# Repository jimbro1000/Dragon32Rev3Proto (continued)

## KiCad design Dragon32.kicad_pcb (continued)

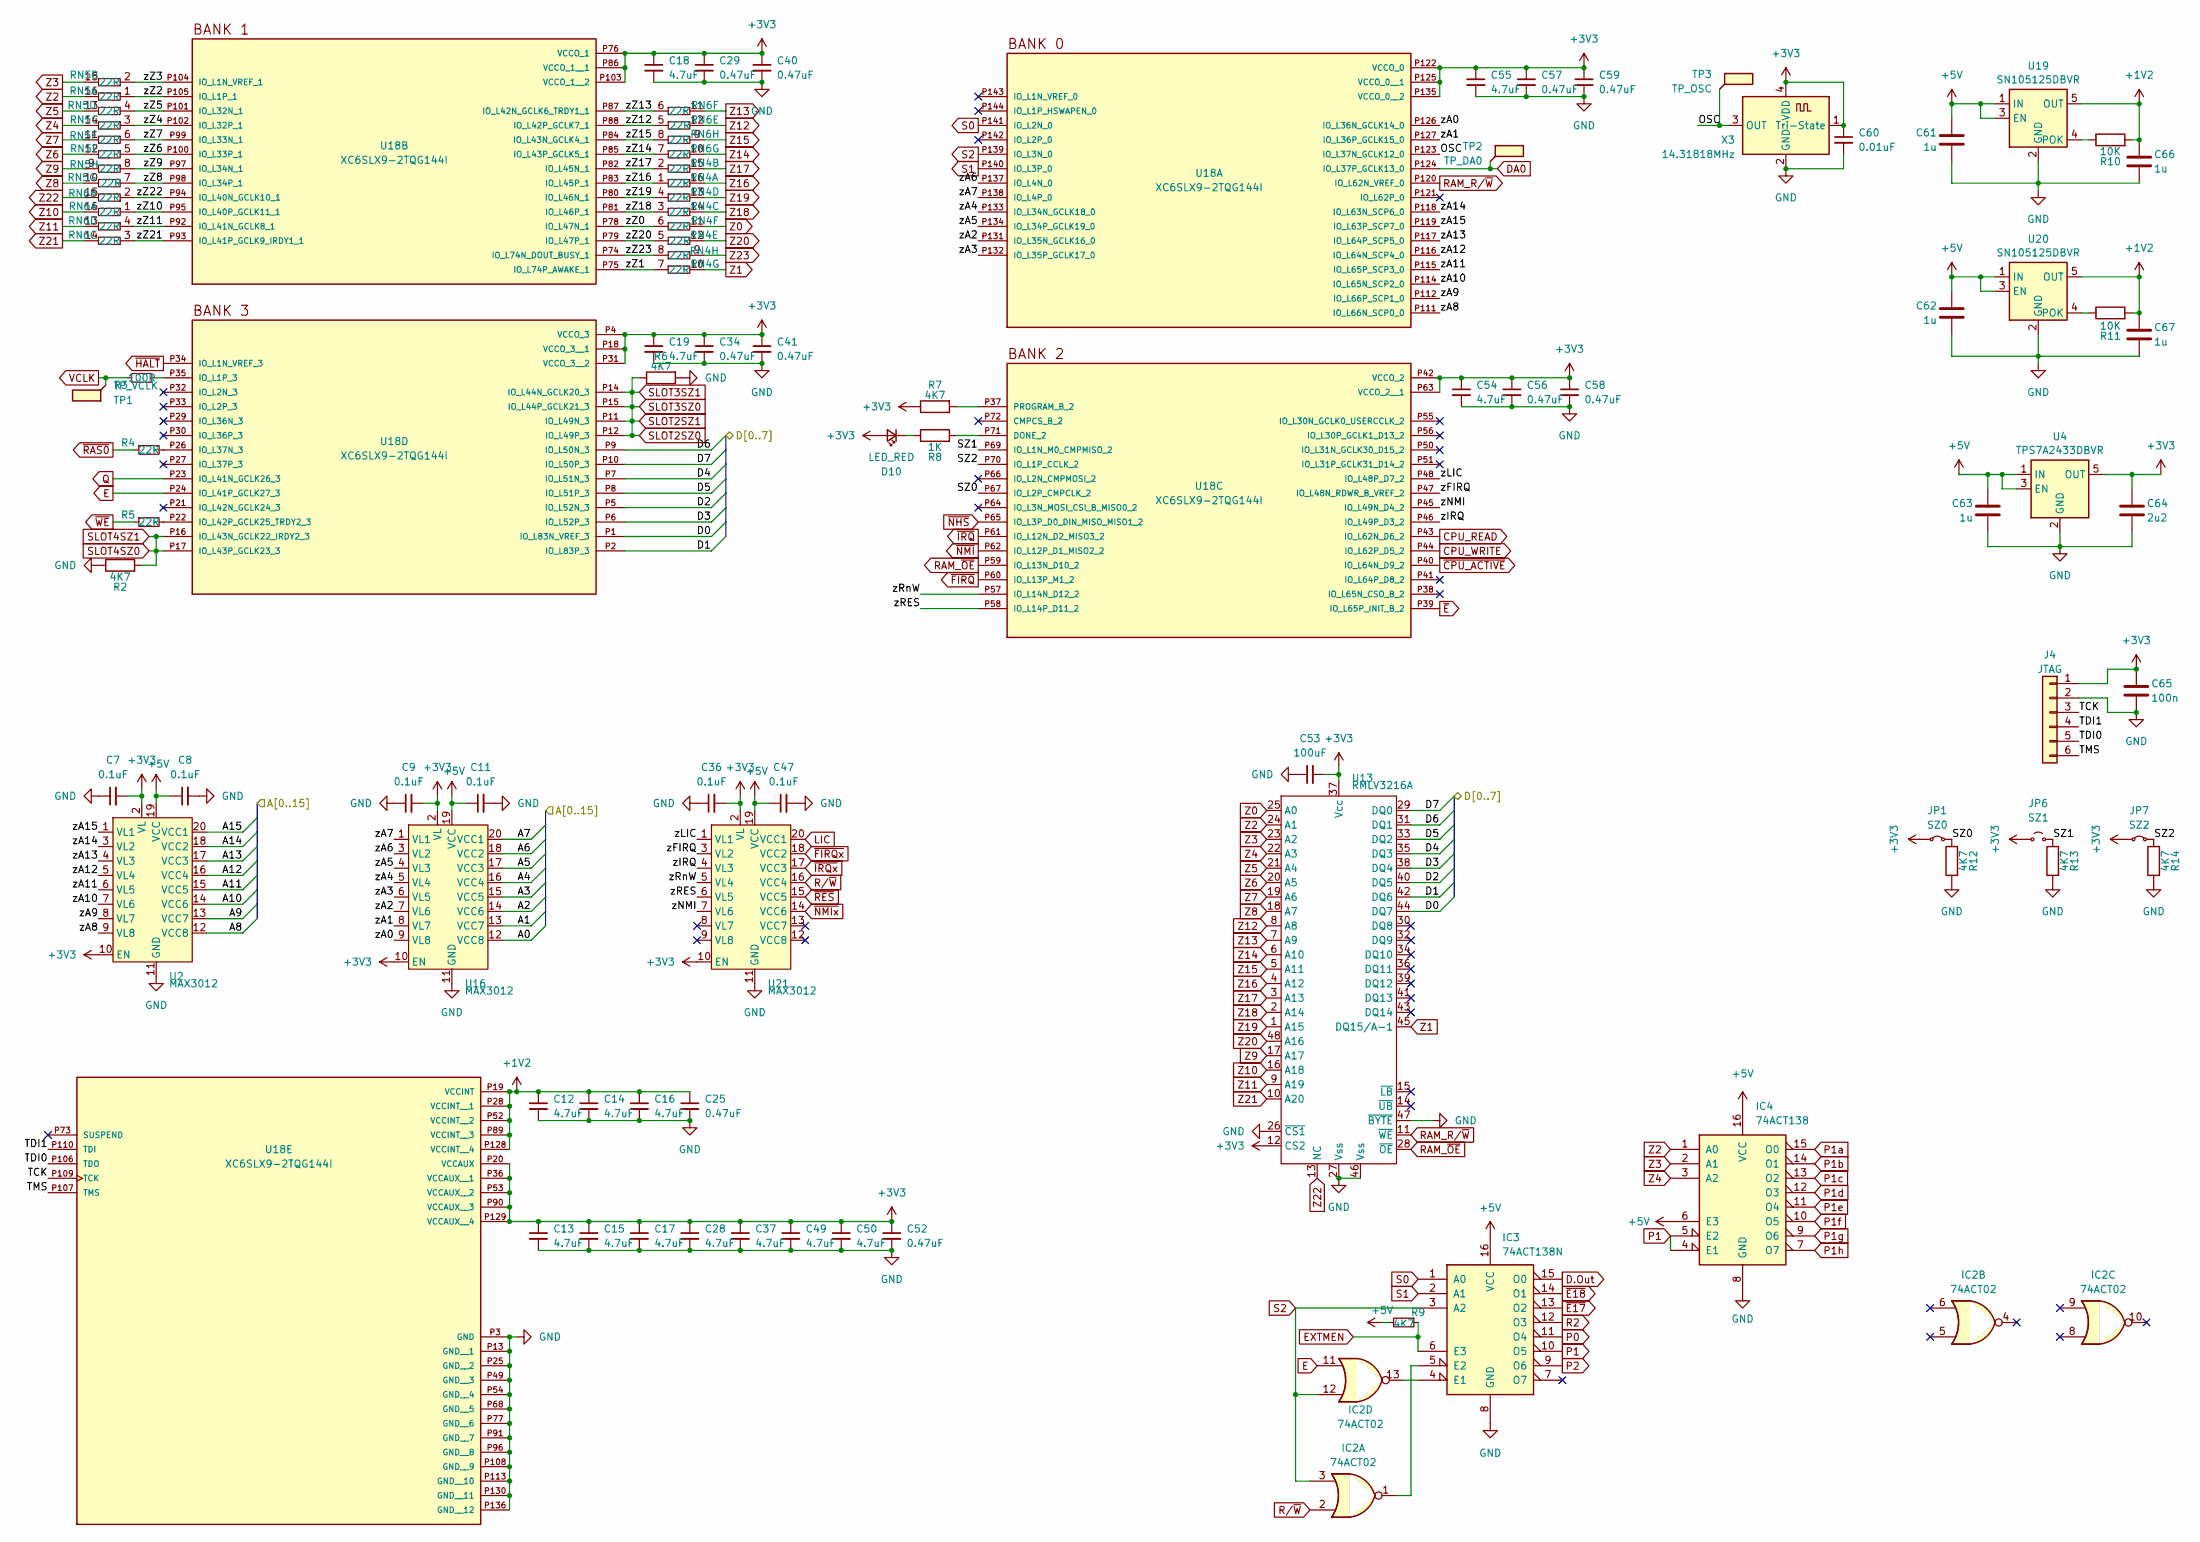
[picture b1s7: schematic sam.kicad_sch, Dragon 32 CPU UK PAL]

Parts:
C7, C8, C9, C11, C36, C47: 0.1uF; C_0805_2012Metric_Pad1.18x1.45mm_HandSolder; DigiKey 399-C0805C104K4RAC7800CT-ND
C12, C13, C14, C15, C16, C17, C18, C19, C28, C37, C49, C50, C54, C55: 4.7uF; C_0805_2012Metric_Pad1.18x1.45mm_HandSolder; DigiKey 399-C0805C475K4RAC7800CT-ND
C25, C29, C34, C40, C41, C52, C56, C57, C58, C59: 0.47uF; C_0805_2012Metric_Pad1.18x1.45mm_HandSolder; DigiKey 399-C0805C474K4RAC7800CT-ND
C53: 100uF; C_0805_2012Metric_Pad1.18x1.45mm_HandSolder
C60: 0.01uF; C_0805_2012Metric_Pad1.18x1.45mm_HandSolder; DigiKey 399-C0805C103K4RAC7800CT-ND
C61, C62, C66, C67: 1u; C_0805_2012Metric_Pad1.18x1.45mm_HandSolder; DigiKey 399-C0805C105K4RAC7800CT-ND
C63: 1u; C_0805_2012Metric_Pad1.18x1.45mm_HandSolder; LCSC Part C77080
C64: 2u2; C_0805_2012Metric_Pad1.18x1.45mm_HandSolder; LCSC Part C961513
C65: 100n; C_0805_2012Metric_Pad1.18x1.45mm_HandSolder; JLCPCB BOM 0
D10: LED_RED; LED_0805_2012Metric; DigiKey 67-SML-LXF0805SRD-TRCT-ND
IC2: 74ACT02; SOIC-14_3.9x8.7mm_P1.27mm; DigiKey MC74ACT02DR2GOSCT-ND
IC3: 74ACT138N; SOIC-16W_7.5x10.3mm_P1.27mm; DigiKey 74ACT138SCXCT-ND
IC4: 74ACT138; SOIC-16W_7.5x10.3mm_P1.27mm; DigiKey 74ACT138SCXCT-ND
J4: JTAG; PinHeader_1x06_P2.54mm_Vertical; JLCPCB BOM 0
JP1: SZ0; SolderJumper-2_P1.3mm_Bridged_Pad1.0x1.5mm
JP6: SZ1; SolderJumper-2_P1.3mm_Open_Pad1.0x1.5mm
JP7: SZ2; SolderJumper-2_P1.3mm_Bridged_Pad1.0x1.5mm
R2, R6, R7, R12, R13, R14: 4K7; R_0805_2012Metric_Pad1.20x1.40mm_HandSolder; DigiKey 541-4131-1-ND
R3: 100R; R_0805_2012Metric_Pad1.20x1.40mm_HandSolder; DigiKey RNCP0805FTD100RCT-ND
R4, R5: 22R; R_0805_2012Metric_Pad1.20x1.40mm_HandSolder; DigiKey RPC0805JT22R0CT-ND
R8: 1K; R_0805_2012Metric_Pad1.20x1.40mm_HandSolder; DigiKey RNCP0805FTD1K00CT-ND
R9: 4K7; R_0805_2012Metric_Pad1.20x1.40mm_HandSolder; DigiKey CF14JT4K70CT-ND
R10, R11: 10K; R_0805_2012Metric_Pad1.20x1.40mm_HandSolder; DigiKey RNCP0805FTD10K0CT-ND
RN4, RN6: 22R; SOIC-16W_5.3x10.2mm_P1.27mm
RN5: 22R; SOIC-16W_5.3x10.2mm_P1.27mm; DigiKey 4816P-T01-220LF-ND
TP1: TP_VCLK; TestPoint_Loop_D1.80mm_Drill1.0mm_Beaded
TP2: TP_DA0; TestPoint_Loop_D1.80mm_Drill1.0mm_Beaded
TP3: TP_OSC; TestPoint_Loop_D1.80mm_Drill1.0mm_Beaded
U2, U16, U21: MAX3012; TSSOP-20_4.4x6.5mm_P0.65mm; DigiKey MAX3012EUP+-ND
U4: TPS7A2433DBVR; SOT-23-5; LCSC Part C2866134
U13: RMLV3216A; TSOP-I-48_18.4x12mm_P0.5mm; DigiKey RMLV3216AGSA-5S2#AA0-ND
U18: XC6SLX9-2TQG144I; AMD-LQFP-144; DigiKey 122-1748-ND
U19, U20: SN105125DBVR; SOT-23-5; DigiKey 296-15347-1-ND
X3: 14.31818MHz; Oscillator_SMD_ECS_2520MV-xxx-xx-4Pin_2.5x2.0mm; DigiKey XC1405CT-ND

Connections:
+1V2: C12.1, C14.1, C16.1, C25.1, C66.1, C67.1, R10.2, R11.2, U18.P19 (VCCINT), U18.P28 (VCCINT__1), U18.P52 (VCCINT__2), U18.P89 (VCCINT__3), U18.P128 (VCCINT__4), U19.5 (OUT), U20.5 (OUT)
/MPU/A0: U16.12 (VCC8); also elsewhere on the board
/MPU/A1: U16.13 (VCC7); also elsewhere on the board
/MPU/A2: U16.14 (VCC6); also elsewhere on the board
/MPU/A3: U16.15 (VCC5); also elsewhere on the board
/MPU/A4: U16.16 (VCC4); also elsewhere on the board
/MPU/A5: U16.17 (VCC3); also elsewhere on the board
/MPU/A6: U16.18 (VCC2); also elsewhere on the board
/MPU/A7: U16.20 (VCC1); also elsewhere on the board
/MPU/A13: U2.17 (VCC3); also elsewhere on the board
/MPU/A14: U2.18 (VCC2); also elsewhere on the board
/MPU/A15: U2.20 (VCC1); also elsewhere on the board
/MPU/D0: U13.44 (DQ7), U18.P1 (IO_L83N_VREF_3); also elsewhere on the board
/MPU/D1: U13.42 (DQ6), U18.P2 (IO_L83P_3); also elsewhere on the board
/MPU/D2: U13.40 (DQ5), U18.P5 (IO_L52N_3); also elsewhere on the board
/MPU/D3: U13.38 (DQ4), U18.P6 (IO_L52P_3); also elsewhere on the board
/MPU/D5: U13.33 (DQ2), U18.P8 (IO_L51P_3); also elsewhere on the board
/SAM/OSC: TP3.1, U18.P123 (IO_L37N_GCLK12_0), X3.3 (OUT)
/SAM/SZ0: JP1.2 (B), R12.1, U18.P67 (IO_L2P_CMPCLK_2)
/SAM/SZ1: JP6.2 (B), R13.1, U18.P69 (IO_L1N_M0_CMPMISO_2)
/SAM/SZ2: JP7.2 (B), R14.1, U18.P70 (IO_L1P_CCLK_2)
/SAM/TCK: J4.3, U18.P109 (TCK)
/SAM/TDI0: J4.5, U18.P106 (TDO)
/SAM/TDI1: J4.4, U18.P110 (TDI)
/SAM/TMS: J4.6, U18.P107 (TMS)
/SAM/zA0: U16.9 (VL8), U18.P126 (IO_L36N_GCLK14_0)
/SAM/zA1: U16.8 (VL7), U18.P127 (IO_L36P_GCLK15_0)
/SAM/zA2: U16.7 (VL6), U18.P131 (IO_L35N_GCLK16_0)
/SAM/zA3: U16.6 (VL5), U18.P132 (IO_L35P_GCLK17_0)
/SAM/zA4: U16.5 (VL4), U18.P133 (IO_L34N_GCLK18_0)
/SAM/zA5: U16.4 (VL3), U18.P134 (IO_L34P_GCLK19_0)
/SAM/zA6: U16.3 (VL2), U18.P137 (IO_L4N_0)
/SAM/zA7: U16.1 (VL1), U18.P138 (IO_L4P_0)
/SAM/zFIRQ: U18.P47 (IO_L48N_RDWR_B_VREF_2), U21.3 (VL2)
/SAM/zIRQ: U18.P46 (IO_L49P_D3_2), U21.4 (VL3)
/SAM/zLIC: U18.P48 (IO_L48P_D7_2), U21.1 (VL1)
/SAM/zNMI: U18.P45 (IO_L49N_D4_2), U21.7 (VL6)
/SAM/zRES: U18.P58 (IO_L14P_D11_2), U21.6 (VL5)
/SAM/zRnW: U18.P57 (IO_L14N_D12_2), U21.5 (VL4)
/SAM/zZ0: RN4.6, U18.P78 (IO_L47N_1)
/SAM/zZ1: RN4.7, U18.P75 (IO_L74P_AWAKE_1)
/SAM/zZ2: RN5.1, U18.P105 (IO_L1P_1)
/SAM/zZ3: RN5.2, U18.P104 (IO_L1N_VREF_1)
/SAM/zZ4: RN5.3, U18.P102 (IO_L32P_1)
/SAM/zZ5: RN5.4, U18.P101 (IO_L32N_1)
/SAM/zZ6: RN5.5, U18.P100 (IO_L33P_1)
/SAM/zZ7: RN5.6, U18.P99 (IO_L33N_1)
/SAM/zZ8: RN5.7, U18.P98 (IO_L34P_1)
/SAM/zZ9: RN5.8, U18.P97 (IO_L34N_1)
/SAM/zZ10: RN6.1, U18.P95 (IO_L40P_GCLK11_1)
/SAM/zZ11: RN6.4, U18.P92 (IO_L41N_GCLK8_1)
/SAM/zZ12: RN6.5, U18.P88 (IO_L42P_GCLK7_1)
/SAM/zZ13: RN6.6, U18.P87 (IO_L42N_GCLK6_TRDY1_1)
/SAM/zZ14: RN6.7, U18.P85 (IO_L43P_GCLK5_1)
/SAM/zZ15: RN6.8, U18.P84 (IO_L43N_GCLK4_1)
/SAM/zZ16: RN4.1, U18.P83 (IO_L45P_1)
/SAM/zZ17: RN4.2, U18.P82 (IO_L45N_1)
/SAM/zZ18: RN4.3, U18.P81 (IO_L46P_1)
/SAM/zZ19: RN4.4, U18.P80 (IO_L46N_1)
/SAM/zZ20: RN4.5, U18.P79 (IO_L47P_1)
/SAM/zZ21: RN6.3, U18.P93 (IO_L41P_GCLK9_IRDY1_1)
/SAM/zZ22: RN6.2, U18.P94 (IO_L40N_GCLK10_1)
/SAM/zZ23: RN4.8, U18.P74 (IO_L74N_DOUT_BUSY_1)
CPU_READ: U18.P43 (IO_L62N_D6_2); also elsewhere on the board
CPU_WRITE: U18.P44 (IO_L62P_D5_2); also elsewhere on the board
D.Out: IC3.15 (O0)
DA0: TP2.1, U18.P124 (IO_L37P_GCLK13_0); also elsewhere on the board
E: IC2.11, U18.P24 (IO_L41P_GCLK27_3); also elsewhere on the board
EXTMEN: IC3.6 (E3), R9.1; also elsewhere on the board
LIC: U21.20 (VCC1)
unnamed: D10.1 (K), R8.1
unnamed: IC2.13, IC3.4 (E1)
unnamed: IC2.1, IC3.5 (E2)
unnamed: R8.2, U18.P71 (DONE_2)
unnamed: R7.2, U18.P37 (PROGRAM_B_2)
unnamed: R3.2, U18.P35 (IO_L1P_3)
unnamed: R4.2, U18.P26 (IO_L37N_3)
unnamed: R5.2, U18.P22 (IO_L42P_GCLK25_TRDY2_3)
unnamed: R10.1, U19.4 (POK)
unnamed: R11.1, U20.4 (POK)
P0: IC3.11 (O4); also elsewhere on the board
P1: IC3.10 (O5), IC4.4 (E1), IC4.5 (E2)
P1a: IC4.15 (O0); also elsewhere on the board
P1b: IC4.14 (O1); also elsewhere on the board
P1c: IC4.13 (O2); also elsewhere on the board
P1d: IC4.12 (O3); also elsewhere on the board
P1e: IC4.11 (O4)
P1f: IC4.10 (O5)
P1g: IC4.9 (O6)
P1h: IC4.7 (O7)
P2: IC3.9 (O6); also elsewhere on the board
Q: U18.P23 (IO_L41N_GCLK26_3); also elsewhere on the board
R2: IC3.12 (O3); also elsewhere on the board
RAM_R/~W: U13.11 (~WE), U18.P120 (IO_L62N_VREF_0)
RAM_~OE: U13.28 (~OE), U18.P59 (IO_L13N_D10_2)
R/~W: IC2.2, U21.16 (VCC4); also elsewhere on the board
S0: IC3.1 (A0), U18.P141 (IO_L2N_0)
S1: IC3.2 (A1), U18.P140 (IO_L3P_0)
S2: IC2.3, IC2.12, IC3.3 (A2), U18.P139 (IO_L3N_0)
SLOT2SZ0: R6.1, U18.P11 (IO_L49N_3), U18.P12 (IO_L49P_3), U18.P14 (IO_L44N_GCLK20_3), U18.P15 (IO_L44P_GCLK21_3)
SLOT4SZ0: R2.2, U18.P16 (IO_L43N_GCLK22_IRDY2_3), U18.P17 (IO_L43P_GCLK23_3)
VCLK: R3.1, TP1.1; also elsewhere on the board
Z0: RN4.11, U13.25 (A0); also elsewhere on the board
Z1: RN4.10, U13.45 (DQ15/A-1); also elsewhere on the board
Z2: IC4.1 (A0), RN5.16, U13.24 (A1); also elsewhere on the board
Z3: IC4.2 (A1), RN5.15, U13.23 (A2); also elsewhere on the board
Z4: IC4.3 (A2), RN5.14, U13.22 (A3); also elsewhere on the board
Z5: RN5.13, U13.21 (A4); also elsewhere on the board
Z6: RN5.12, U13.20 (A5); also elsewhere on the board
Z7: RN5.11, U13.19 (A6); also elsewhere on the board
Z8: RN5.10, U13.18 (A7); also elsewhere on the board
Z9: RN5.9, U13.17 (A17); also elsewhere on the board
Z10: RN6.16, U13.16 (A18); also elsewhere on the board
Z11: RN6.13, U13.9 (A19); also elsewhere on the board
Z12: RN6.12, U13.8 (A8); also elsewhere on the board
Z13: RN6.11, U13.7 (A9); also elsewhere on the board
Z14: RN6.10, U13.6 (A10); also elsewhere on the board
Z15: RN6.9, U13.5 (A11); also elsewhere on the board
Z16: RN4.16, U13.4 (A12); also elsewhere on the board
Z17: RN4.15, U13.3 (A13); also elsewhere on the board
Z18: RN4.14, U13.2 (A14); also elsewhere on the board
Z19: RN4.13, U13.1 (A15)
Z20: RN4.12, U13.48 (A16)
Z21: RN6.14, U13.10 (A20)
Z22: RN6.15, U13.13 (NC)
Z23: RN4.9
~CPU_ACTIVE: U18.P40 (IO_L64N_D9_2)
~E17: IC3.13 (O2)
~E18: IC3.14 (O1)
~E: U18.P39 (IO_L65P_INIT_B_2); also elsewhere on the board
~FIRQx: U21.18 (VCC2); also elsewhere on the board
~FIRQ: U18.P60 (IO_L13P_M1_2); also elsewhere on the board
~HALT: U18.P34 (IO_L1N_VREF_3); also elsewhere on the board
~IRQx: U21.17 (VCC3); also elsewhere on the board
~IRQ: U18.P61 (IO_L12N_D2_MISO3_2); also elsewhere on the board
~NHS: U18.P65 (IO_L3P_D0_DIN_MISO_MISO1_2); also elsewhere on the board
~NMIx: U21.14 (VCC6); also elsewhere on the board
~NMI: U18.P62 (IO_L12P_D1_MISO2_2); also elsewhere on the board
~RAS0: R4.1; also elsewhere on the board
~RES: U21.15 (VCC5); also elsewhere on the board
~WE: R5.1

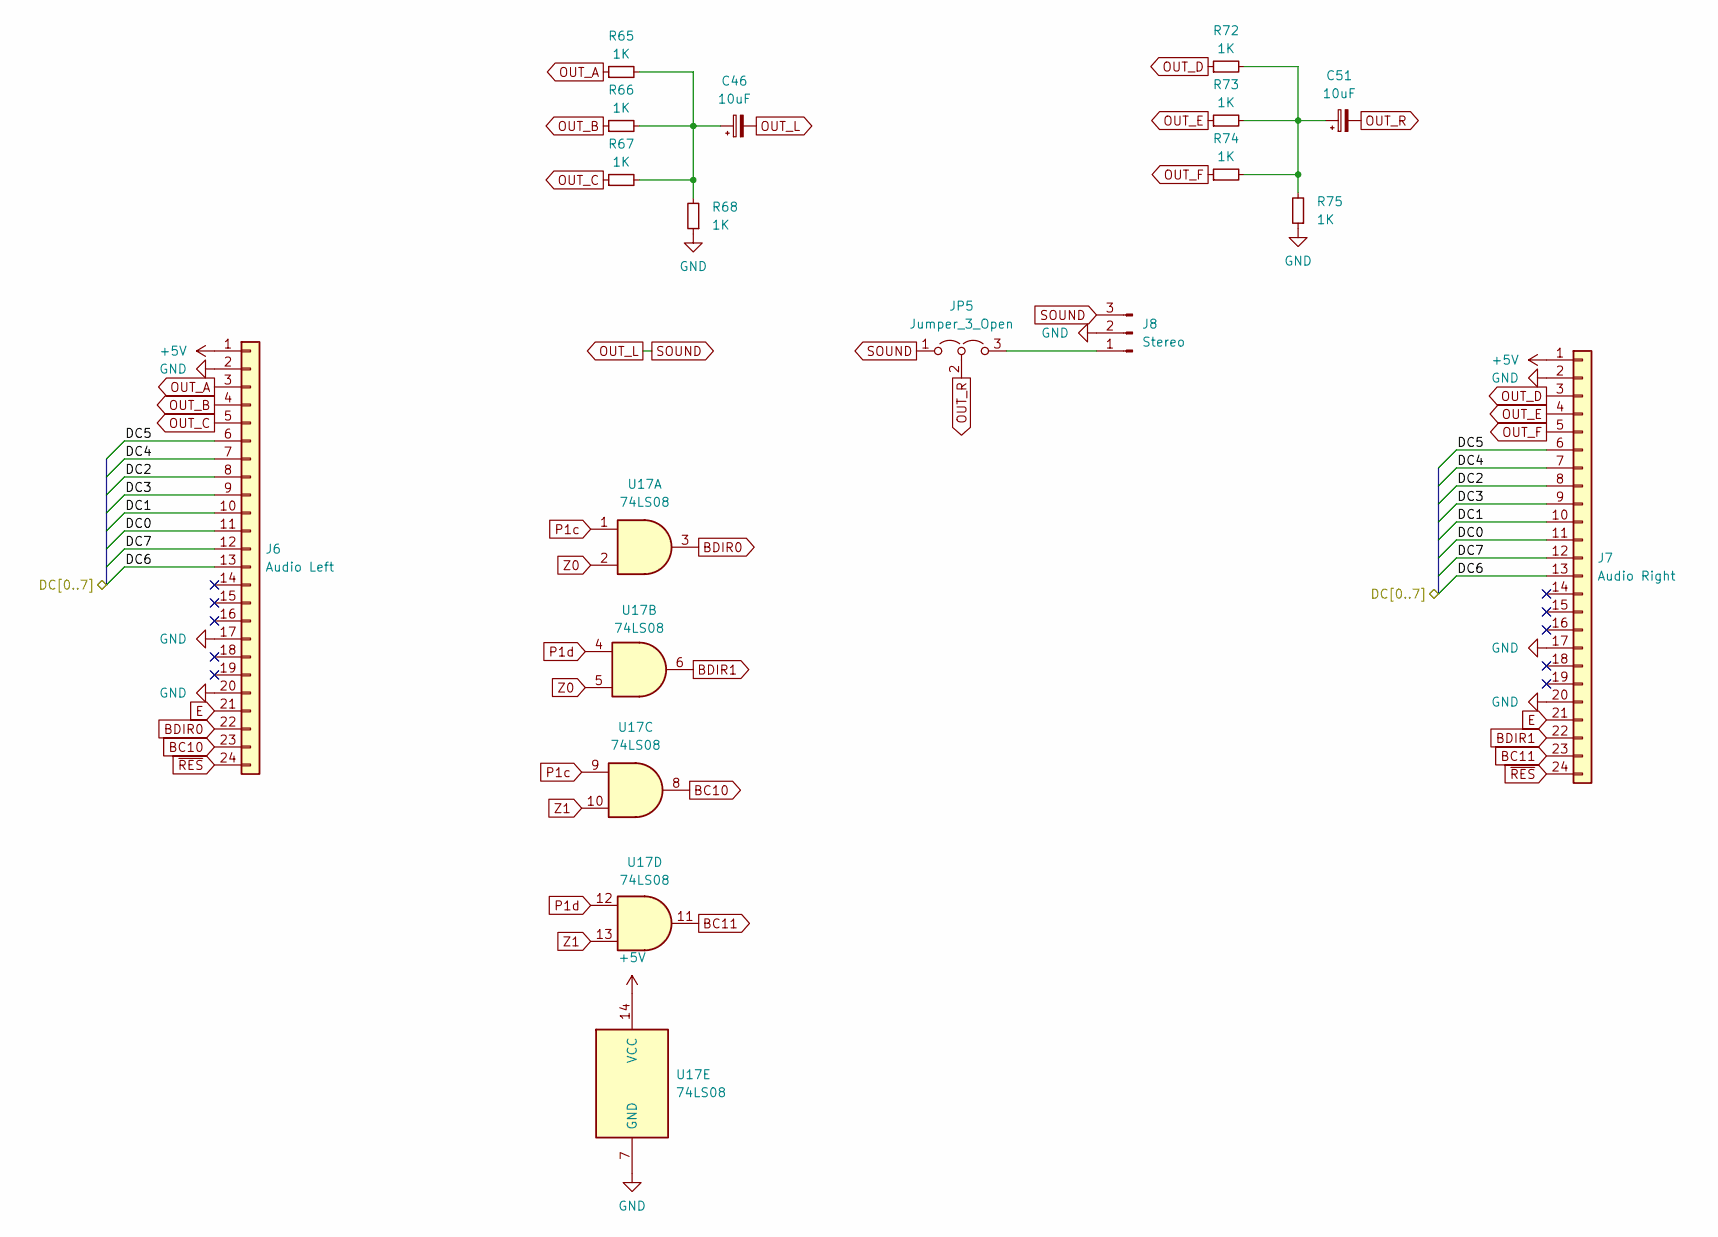
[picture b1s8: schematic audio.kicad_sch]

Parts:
C46, C51: 10uF; CP_Elec_5x3
J6: Audio Left; AY-QTHT
J7: Audio Right; AY-QTHT
J8: Stereo; PinHeader_1x03_P2.54mm_Vertical
JP5: Jumper_3_Open; PinHeader_1x03_P2.54mm_Vertical
R65, R66, R67, R68, R72, R73, R74, R75: 1K; R_0805_2012Metric_Pad1.20x1.40mm_HandSolder
U17: 74LS08; SO-14_3.9x8.65mm_P1.27mm

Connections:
/AUDIO/DC0: J6.11, J7.11; also elsewhere on the board
/AUDIO/DC1: J6.10, J7.10; also elsewhere on the board
/AUDIO/DC2: J6.8, J7.8; also elsewhere on the board
/AUDIO/DC3: J6.9, J7.9; also elsewhere on the board
/AUDIO/DC4: J6.7, J7.7; also elsewhere on the board
/AUDIO/DC5: J6.6, J7.6; also elsewhere on the board
/AUDIO/DC6: J6.13, J7.13; also elsewhere on the board
/AUDIO/DC7: J6.12, J7.12; also elsewhere on the board
BC10: J6.23, U17.8
BC11: J7.23, U17.11
BDIR0: J6.22, U17.3
BDIR1: J7.22, U17.6
E: J6.21, J7.21; also elsewhere on the board
unnamed: C46.1, R65.2, R66.2, R67.2, R68.2
unnamed: C51.1, R72.2, R73.2, R74.2, R75.2
unnamed: J8.1, JP5.3 (B)
OUT_A: J6.3, R65.1
OUT_B: J6.4, R66.1
OUT_C: J6.5, R67.1
OUT_D: J7.3, R72.1
OUT_E: J7.4, R73.1
OUT_F: J7.5, R74.1
OUT_L: C46.2, J8.3, JP5.1 (A); also elsewhere on the board
OUT_R: C51.2, JP5.2 (C)
P1c: U17.1, U17.9; also elsewhere on the board
P1d: U17.4, U17.12; also elsewhere on the board
Z0: U17.2, U17.5; also elsewhere on the board
Z1: U17.10, U17.13; also elsewhere on the board
~RES: J6.24, J7.24; also elsewhere on the board

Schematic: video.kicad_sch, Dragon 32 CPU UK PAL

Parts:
J1: Video Output Female; PinSocket_1x05_P2.54mm_Vertical
J2: Board Interconnect Female; PinSocket_2x11_P2.54mm_Vertical
J3: Conn_02x08_Odd_Even; PinSocket_2x08_P2.54mm_Vertical
PL6: Conn_01x09_Male; Molex_KK-396_A-41791-0009_1x09_P3.96mm_Vertical; DigiKey 2057-LHD-09-TS-ND

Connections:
+12V: PL6.9; also elsewhere on the board
-5V: J1.3, PL6.7; also elsewhere on the board
/MPU/D0: J2.3; also elsewhere on the board
/MPU/D1: J2.5; also elsewhere on the board
/MPU/D2: J2.7; also elsewhere on the board
/MPU/D3: J2.9; also elsewhere on the board
/MPU/D5: J2.13; also elsewhere on the board
BIAS: J1.1, PL6.1
CSS: J2.19; also elsewhere on the board
DA0: J2.6; also elsewhere on the board
E: J3.16; also elsewhere on the board
GM0: J2.14; also elsewhere on the board
GM1: J2.12; also elsewhere on the board
GM2: J2.10; also elsewhere on the board
OUT_L: PL6.3; also elsewhere on the board
P1b: J3.12; also elsewhere on the board
R/~W: J3.14; also elsewhere on the board
VCLK: J2.18; also elsewhere on the board
VID OUT: J1.4, PL6.4
~A/G: J2.20; also elsewhere on the board
~FS: J2.22; also elsewhere on the board
~NHS: J2.8; also elsewhere on the board
~RAS0: J2.16; also elsewhere on the board

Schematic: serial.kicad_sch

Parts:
C2, C20, C21, C24: 10u; CP_Elec_5x5.3
C10: 100n; C_0805_2012Metric_Pad1.18x1.45mm_HandSolder; not fitted
PL9: Serial; DIN-7_DELTRON_671-0701_Horizontal; not fitted
R44, R53: 4K7; R_0805_2012Metric_Pad1.20x1.40mm_HandSolder; DigiKey CF14JT4K70CT-ND; not fitted
U7: MAX232; SOIC-16_3.9x9.9mm_P1.27mm; DigiKey 296-14619-1-ND
U12: W65C51; PLCC-28_SMD-Socket; not fitted
X2: 1.8432MHz; Crystal_HC18-U_Horizontal_1EP_style2; not fitted

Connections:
+12V: R44.2; also elsewhere on the board
-5V: R53.2; also elsewhere on the board
/AUDIO/DC0: U12.18 (D0); also elsewhere on the board
/AUDIO/DC1: U12.19 (D1); also elsewhere on the board
/AUDIO/DC2: U12.20 (D2); also elsewhere on the board
/AUDIO/DC3: U12.21 (D3); also elsewhere on the board
/AUDIO/DC4: U12.22 (D4); also elsewhere on the board
/AUDIO/DC5: U12.23 (D5); also elsewhere on the board
/AUDIO/DC6: U12.24 (D6); also elsewhere on the board
/AUDIO/DC7: U12.25 (D7); also elsewhere on the board
/Serial/RxD: U7.12 (R1OUT), U12.12 (RXD)
/Serial/TxD: U7.11 (T1IN), U12.10 (TXD)
/Serial/xRxD: PL9.5, U7.13 (R1IN)
/Serial/xTxD: PL9.6, U7.14 (T1OUT)
/Serial/x~CTS: PL9.2, U7.8 (R2IN)
/Serial/x~DTR: PL9.4, U7.7 (T2OUT)
/Serial/~CTS: U7.9 (R2OUT), U12.9 (~CTS)
/Serial/~DTR: U7.10 (T2IN), U12.11 (~DTR)
E: U12.27 (E); also elsewhere on the board
unnamed: PL9.3, R44.1
unnamed: PL9.7, R53.1
unnamed: C2.1, U7.1 (C1+)
unnamed: C2.2, U7.3 (C1-)
unnamed: C21.1, U7.4 (C2+)
unnamed: C21.2, U7.5 (C2-)
unnamed: C20.1, U7.2 (VS+)
unnamed: C24.2, U7.6 (VS-)
unnamed: U12.6 (1XTAL), X2.1
unnamed: U12.7 (2XTAL), X2.2
P0: U12.3 (~CS1); also elsewhere on the board
R/~W: U12.28 (R/~W); also elsewhere on the board
Z0: U12.13 (RS0); also elsewhere on the board
Z1: U12.14 (RS1); also elsewhere on the board
Z2: U12.2 (CS0); also elsewhere on the board
~IRQx: U12.26 (~IRQ); also elsewhere on the board
~RES: U12.4 (~RESET); also elsewhere on the board

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
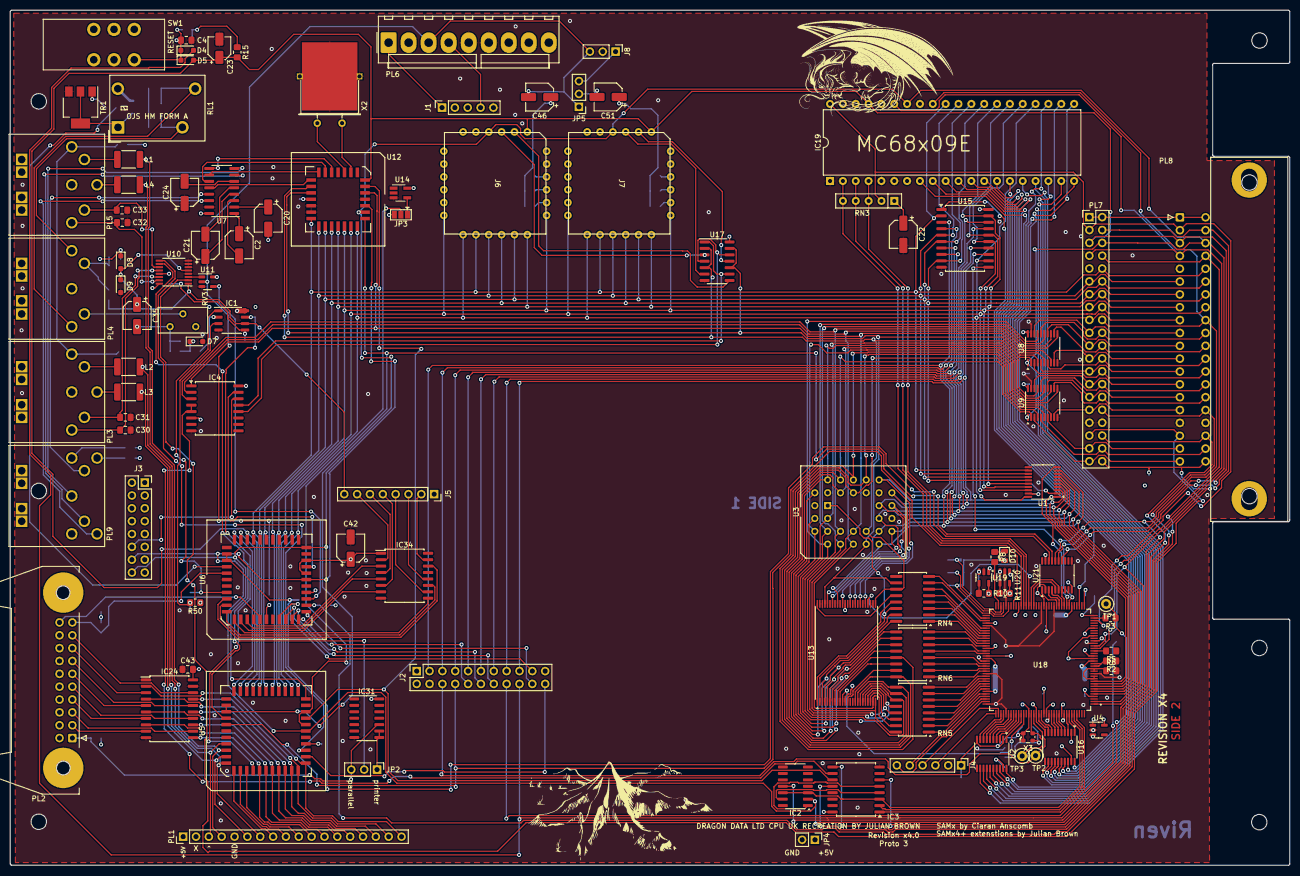
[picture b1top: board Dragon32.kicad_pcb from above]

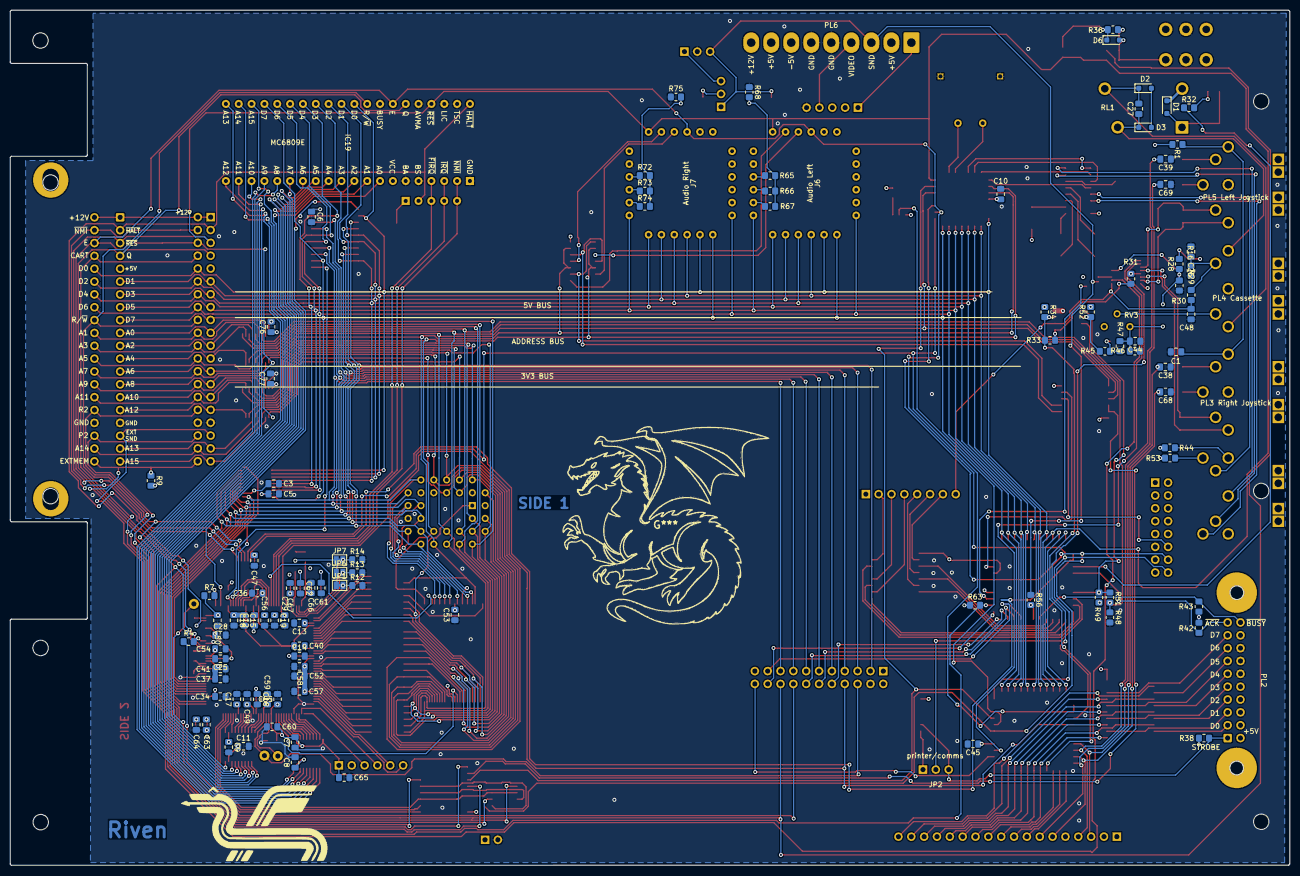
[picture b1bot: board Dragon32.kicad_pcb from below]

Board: 4 copper layers, 252.9 x 169.0 mm, 198 parts (100 on the bottom side), 295 nets.

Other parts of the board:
U10: 4052; TSSOP-16_4.4x5mm_P0.65mm
U11: TS5A3166DBVR; SOT-23-5

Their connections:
CB2: U11.4; also elsewhere on the board
ESND: U10.2 (Y2); also elsewhere on the board
unnamed: U10.3 (Y), U11.1
OUT_L: U11.2; also elsewhere on the board

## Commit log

2023-12-02 move to samx4
2023-12-02 rework board
2023-12-10 serial wiring
2023-12-10 add audio circuits
2023-12-11 complete audio routing
2024-01-07 fix OE timing on SRAM
2024-01-07 update page info
2024-03-04 move -5v
2024-07-07 switch to fpga
2024-07-11 rework traces for FPGA
2024-07-11 remove via in pad
2024-07-12 introduce more artwork
